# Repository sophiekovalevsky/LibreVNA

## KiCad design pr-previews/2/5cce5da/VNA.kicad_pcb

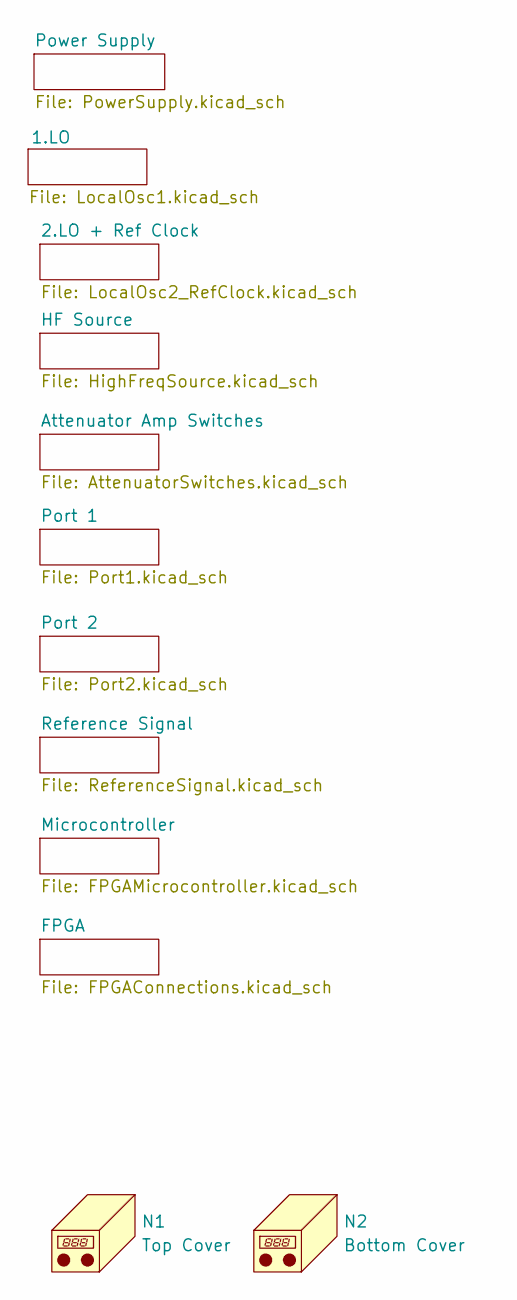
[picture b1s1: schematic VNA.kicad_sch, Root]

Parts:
N1: Top Cover; VNA_COVER_TOP
N2: Bottom Cover; VNA_COVER_BOTTOM

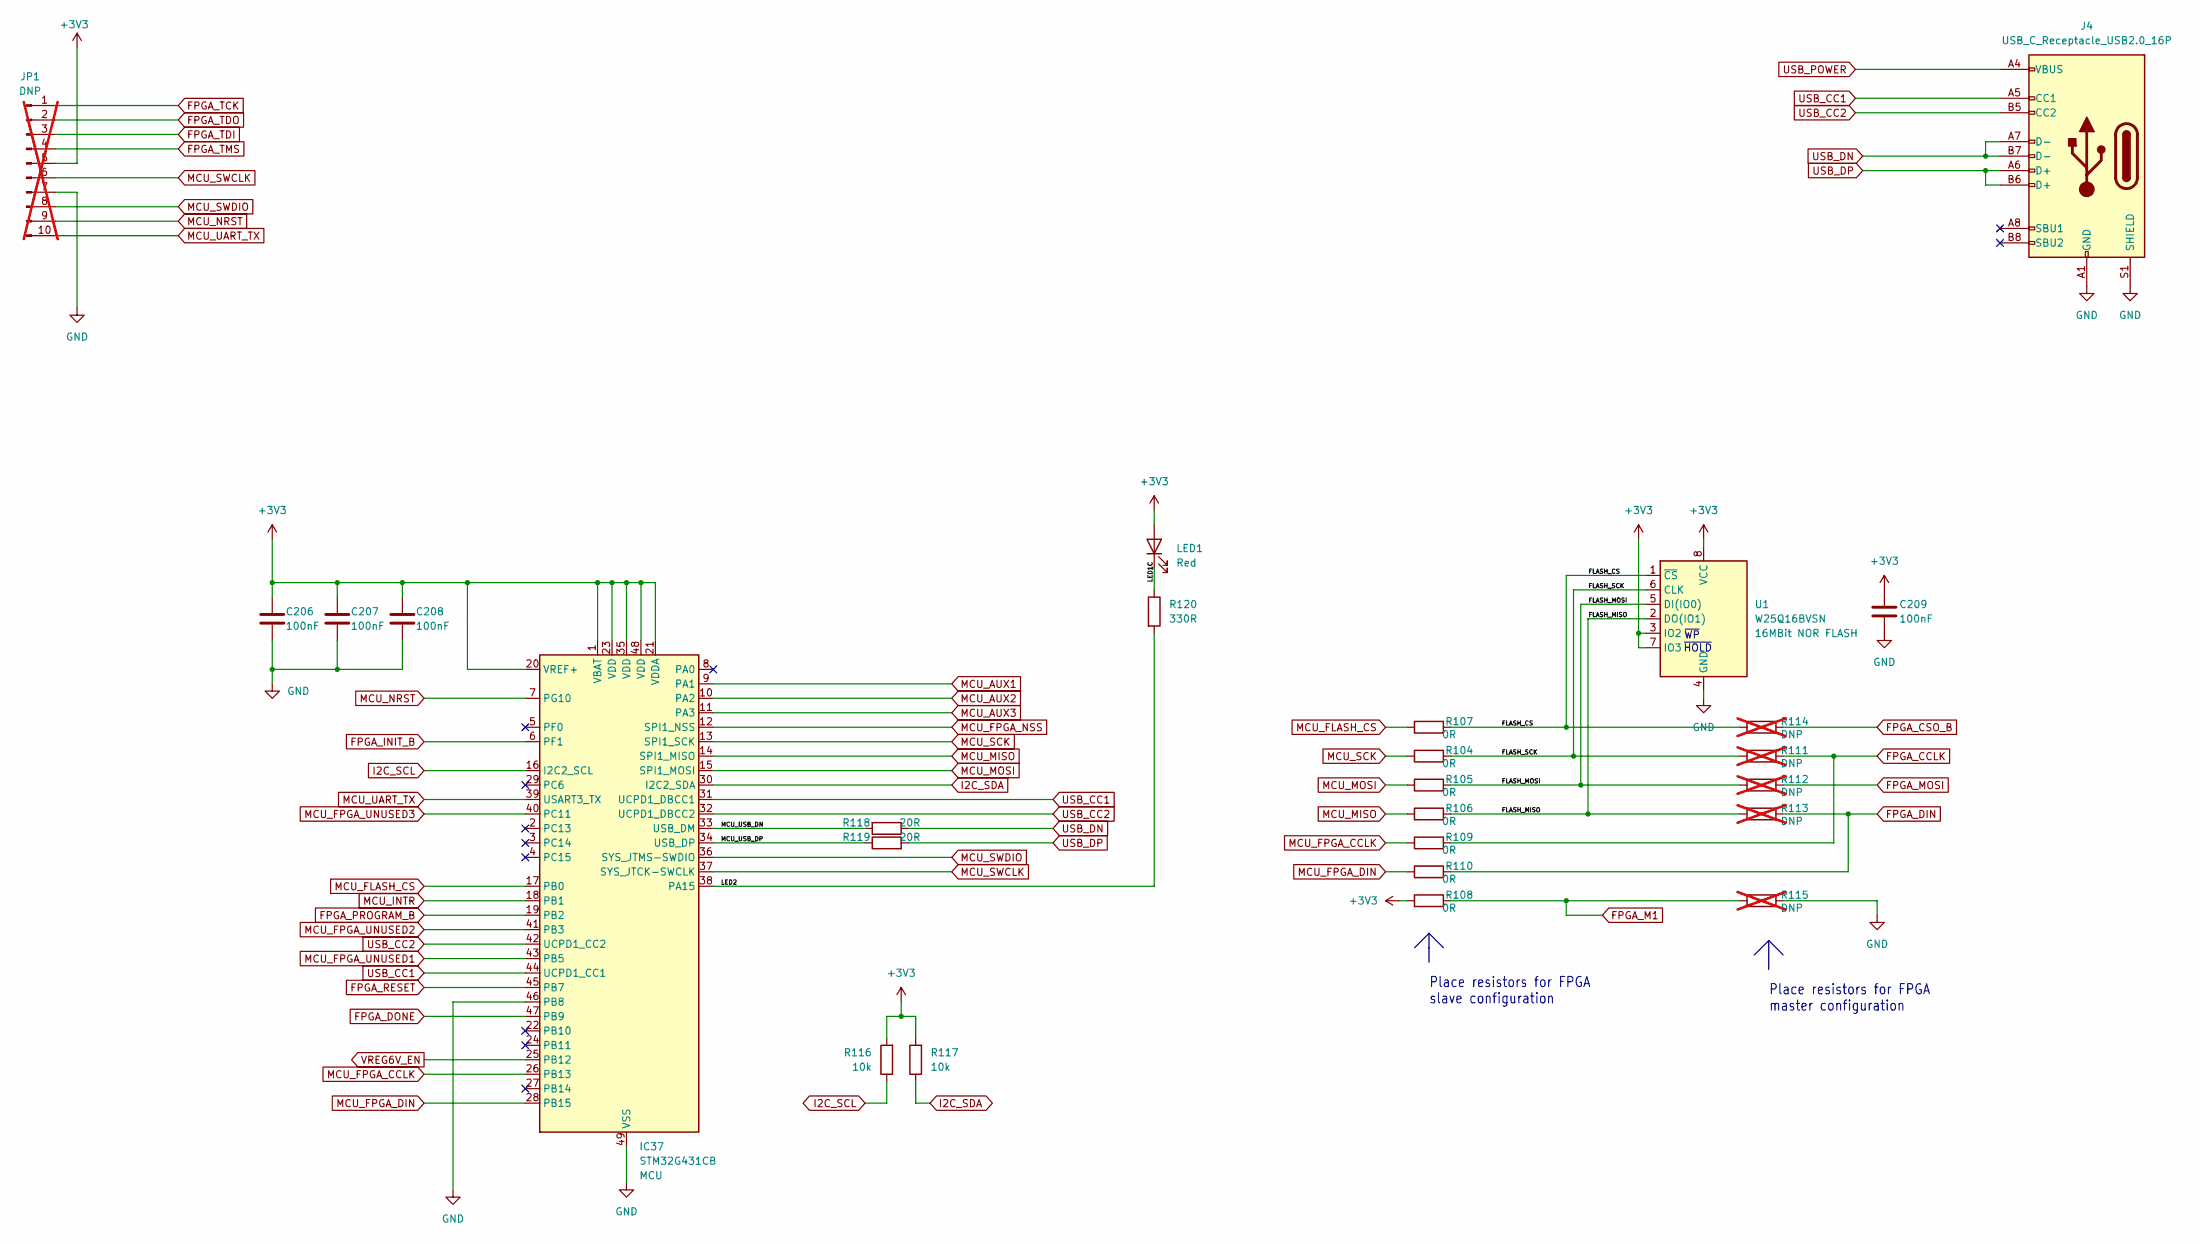
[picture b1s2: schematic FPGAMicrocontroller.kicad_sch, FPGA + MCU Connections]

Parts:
C206, C207, C208, C209: 100nF; C_0402_1005Metric
IC37: STM32G431CB; QFN-48-1EP_7x7mm_P0.5mm_EP5.6x5.6mm; MPN STM32G431CBU6
J4: USB_C_Receptacle_USB2.0_16P; USB_C_Receptacle_GCT_USB4105-xx-A_16P_TopMnt_Horizontal; MPN LCSC C668624
JP1: DNP; PinHeader_1x10_P2.54mm_Horizontal; not fitted
LED1: Red; LED_0603_1608Metric
R104, R105, R106, R107, R108, R109, R110: 0R; R_0402_1005Metric
R111, R112, R113, R114, R115: DNP; R_0402_1005Metric; not fitted
R116, R117: 10k; R_0402_1005Metric
R118, R119: 20R; R_0402_1005Metric
R120: 330R; R_0402_1005Metric
U1: W25Q16BVSN; SOIC-8_3.9x4.9mm_P1.27mm; MPN W25Q16JL

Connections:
+3V3: C206.1, C207.1, C208.1, C209.1, IC37.1 (VBAT), IC37.20 (VREF+), IC37.21 (VDDA), IC37.23 (VDD), IC37.35 (VDD), IC37.48 (VDD), JP1.5, LED1.2 (A), R108.1, R116.2, R117.2, U1.3 (IO2), U1.7 (IO3), U1.8 (VCC); also elsewhere on the board
/Microcontroller/FLASH_CS: R107.2, R114.1, U1.1 (~CS)
/Microcontroller/FLASH_MISO: R106.2, R113.1, U1.2 (DO(IO1))
/Microcontroller/FLASH_MOSI: R105.2, R112.1, U1.5 (DI(IO0))
/Microcontroller/FLASH_SCK: R104.2, R111.1, U1.6 (CLK)
/Microcontroller/LED1C: LED1.1 (K), R120.1
/Microcontroller/LED2: IC37.38 (PA15), R120.2
/Microcontroller/MCU_USB_DN: IC37.33 (USB_DM), R118.2
/Microcontroller/MCU_USB_DP: IC37.34 (USB_DP), R119.1
FPGA_CCLK: R109.2, R111.2; also elsewhere on the board
FPGA_CSO_B: R114.2; also elsewhere on the board
FPGA_DIN: R110.2, R113.2; also elsewhere on the board
FPGA_DONE: IC37.47 (PB9); also elsewhere on the board
FPGA_INIT_B: IC37.6 (PF1); also elsewhere on the board
FPGA_M1: R108.2, R115.1; also elsewhere on the board
FPGA_MOSI: R112.2; also elsewhere on the board
FPGA_PROGRAM_B: IC37.19 (PB2); also elsewhere on the board
FPGA_RESET: IC37.45 (PB7); also elsewhere on the board
FPGA_TCK: JP1.1; also elsewhere on the board
FPGA_TDI: JP1.3; also elsewhere on the board
FPGA_TDO: JP1.2; also elsewhere on the board
FPGA_TMS: JP1.4; also elsewhere on the board
GND: C206.2, C207.2, C208.2, C209.2, IC37.46 (PB8), IC37.49 (VSS), J4.A1 (GND), J4.A12 (GND), J4.B1 (GND), J4.B12 (GND), J4.S1 (SHIELD), JP1.7, R115.2, U1.4 (GND); also elsewhere on the board
I2C_SCL: IC37.16 (I2C2_SCL), R116.1; also elsewhere on the board
I2C_SDA: IC37.30 (I2C2_SDA), R117.1; also elsewhere on the board
MCU_AUX1: IC37.9 (PA1); also elsewhere on the board
MCU_AUX2: IC37.10 (PA2); also elsewhere on the board
MCU_AUX3: IC37.11 (PA3); also elsewhere on the board
MCU_FLASH_CS: IC37.17 (PB0), R107.1
MCU_FPGA_CCLK: IC37.26 (PB13), R109.1
MCU_FPGA_DIN: IC37.28 (PB15), R110.1
MCU_FPGA_NSS: IC37.12 (SPI1_NSS); also elsewhere on the board
MCU_FPGA_UNUSED1: IC37.43 (PB5); also elsewhere on the board
MCU_FPGA_UNUSED2: IC37.41 (PB3); also elsewhere on the board
MCU_FPGA_UNUSED3: IC37.40 (PC11); also elsewhere on the board
MCU_INTR: IC37.18 (PB1); also elsewhere on the board
MCU_MISO: IC37.14 (SPI1_MISO), R106.1; also elsewhere on the board
MCU_MOSI: IC37.15 (SPI1_MOSI), R105.1; also elsewhere on the board
MCU_NRST: IC37.7 (PG10), JP1.9
MCU_SCK: IC37.13 (SPI1_SCK), R104.1; also elsewhere on the board
MCU_SWCLK: IC37.37 (SYS_JTCK-SWCLK), JP1.6
MCU_SWDIO: IC37.36 (SYS_JTMS-SWDIO), JP1.8
MCU_UART_TX: IC37.39 (USART3_TX), JP1.10
USB_CC1: IC37.31 (UCPD1_DBCC1), IC37.44 (UCPD1_CC1), J4.A5 (CC1)
USB_CC2: IC37.32 (UCPD1_DBCC2), IC37.42 (UCPD1_CC2), J4.B5 (CC2)
USB_DN: J4.A7 (D-), J4.B7 (D-), R118.1
USB_DP: J4.A6 (D+), J4.B6 (D+), R119.2
USB_POWER: J4.A4 (VBUS), J4.A9 (VBUS), J4.B4 (VBUS), J4.B9 (VBUS); also elsewhere on the board
VREG6V_EN: IC37.25 (PB12); also elsewhere on the board

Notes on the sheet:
Place resistors for FPGA slave configuration
~{WP}
Place resistors for FPGA master configuration
~{HOLD}

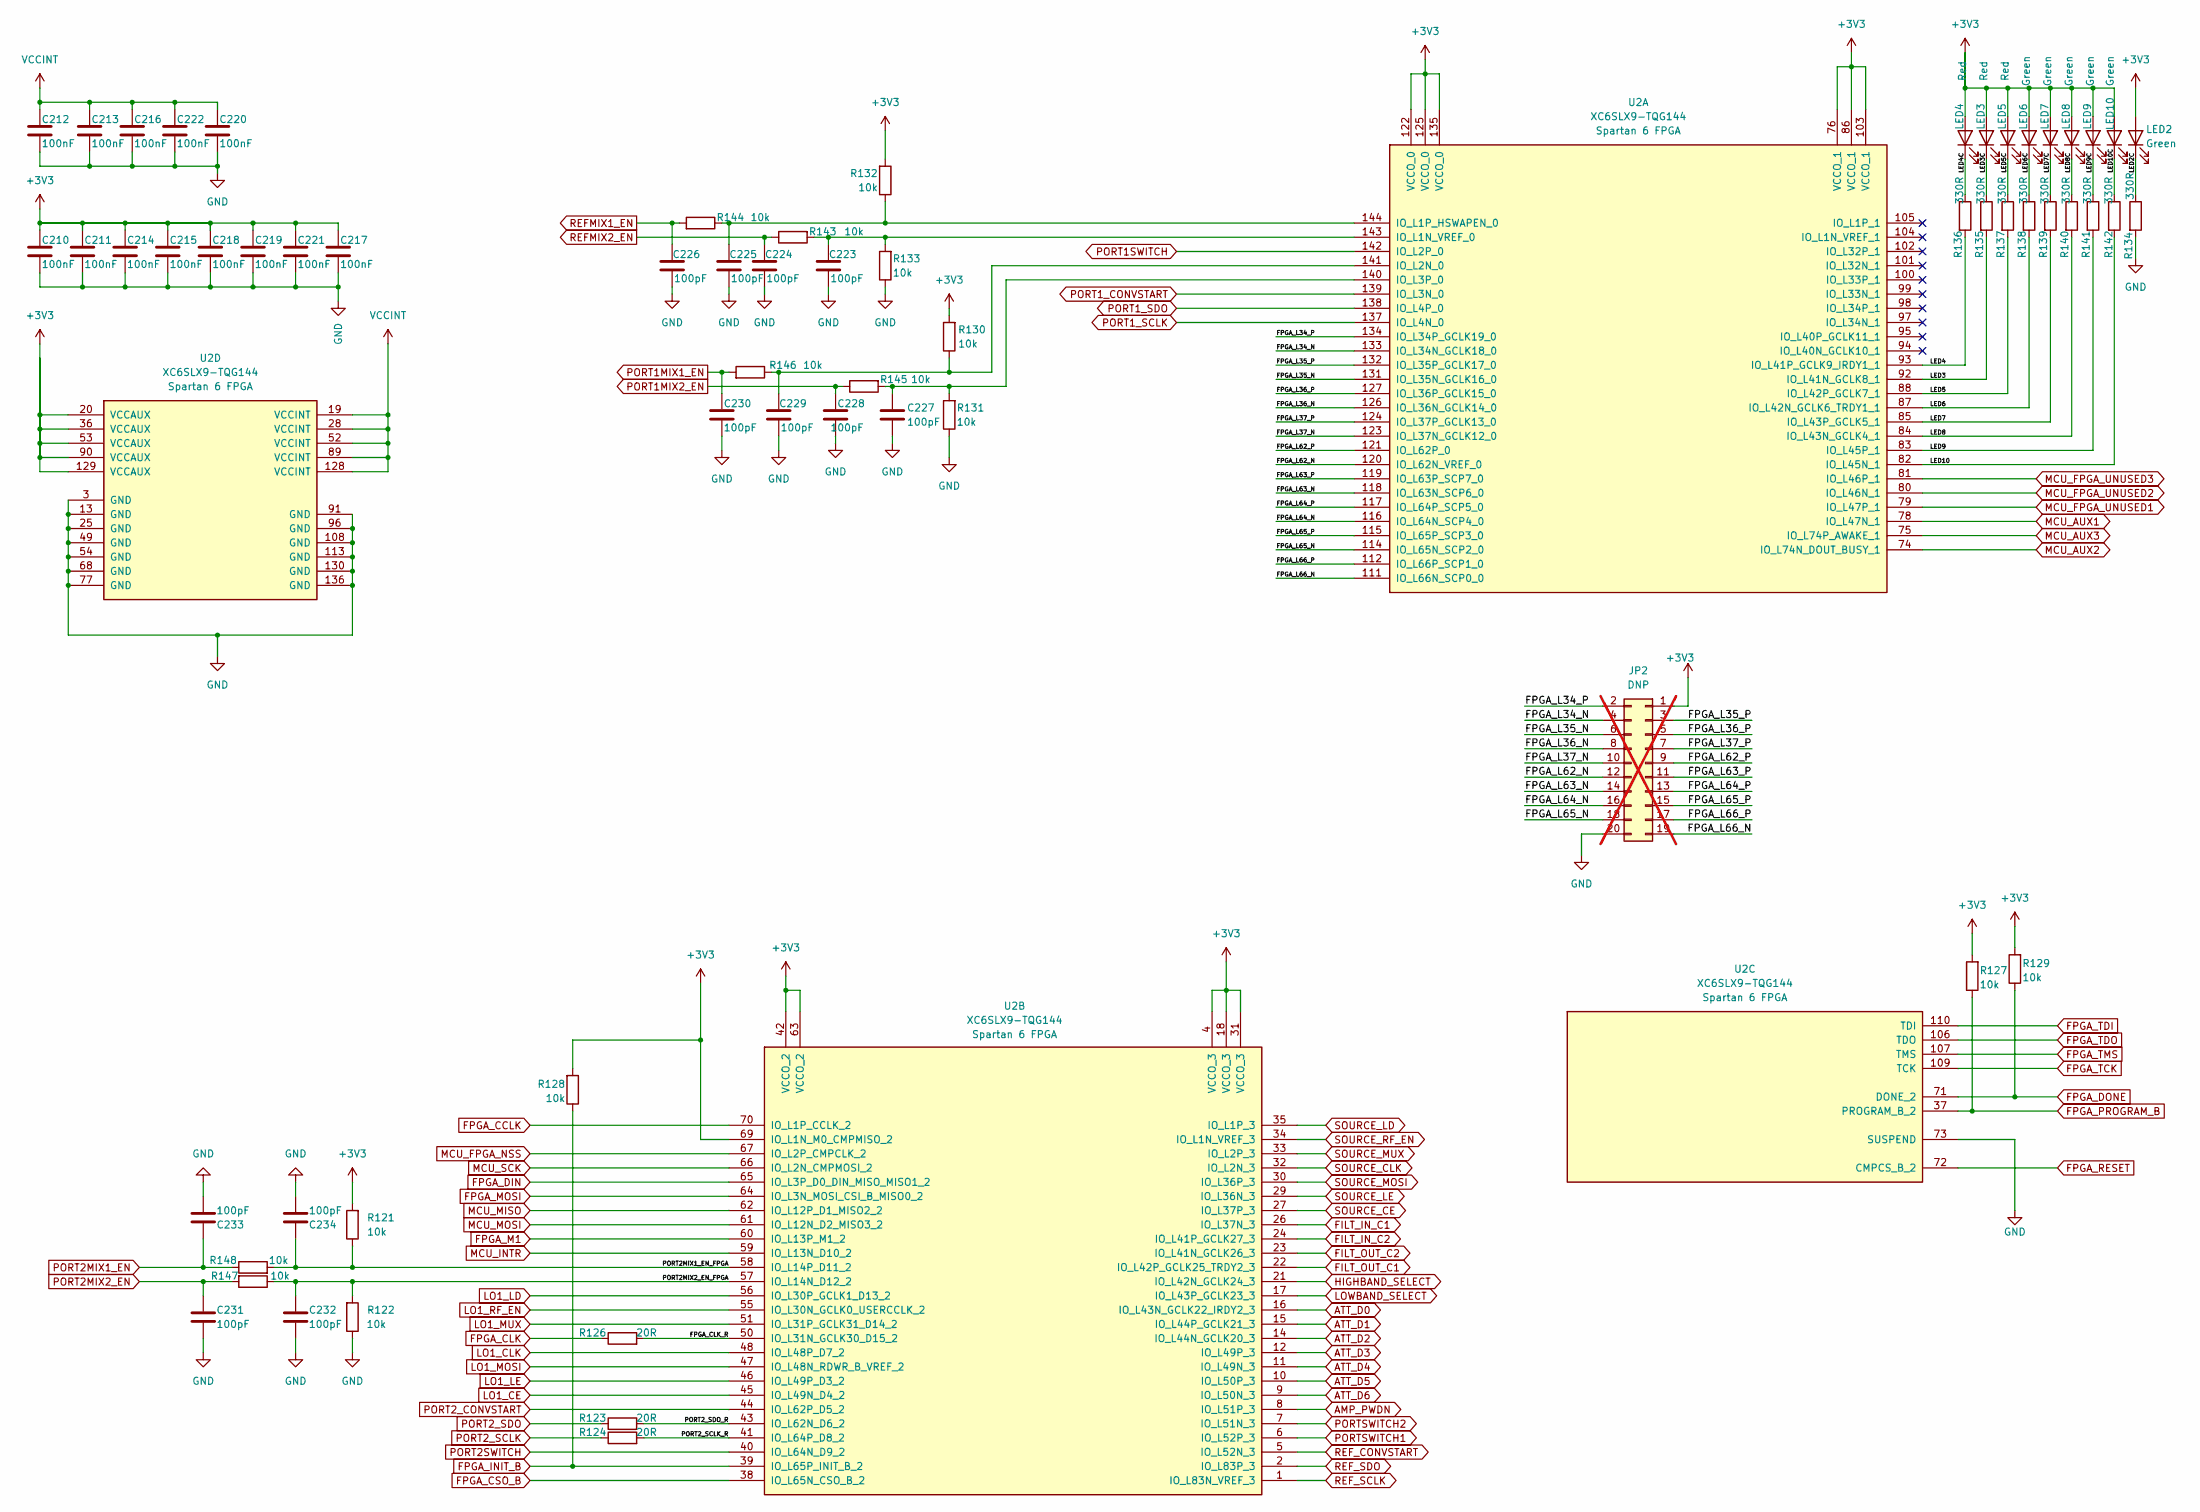
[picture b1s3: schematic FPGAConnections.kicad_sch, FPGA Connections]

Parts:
C210, C211, C212, C213, C214, C215, C216, C217, C218, C219, C220, C221, C222: 100nF; C_0402_1005Metric
C223, C224, C225, C226, C227, C228, C229, C230, C231, C232, C233, C234: 100pF; C_0402_1005Metric
JP2: DNP; PinHeader_2x10_P2.54mm_Vertical; not fitted
LED2, LED6, LED7, LED8, LED9, LED10: Green; LED_0603_1608Metric
LED3, LED4, LED5: Red; LED_0603_1608Metric
R121, R122, R127, R128, R129, R130, R131, R132, R133, R143, R144, R145, R146, R147, R148: 10k; R_0402_1005Metric
R123, R124, R126: 20R; R_0402_1005Metric
R134, R135, R136, R137, R138, R139, R140, R141, R142: 330R; R_0402_1005Metric
U2: XC6SLX9-TQG144; TQFP-144_20x20mm_P0.5mm; MPN XC6SLX9-2TQG144

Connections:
+3V3: C210.1, C211.1, C214.1, C215.1, C217.1, C218.1, C219.1, C221.1, JP2.1, LED2.2 (A), LED3.2 (A), LED4.2 (A), LED5.2 (A), LED6.2 (A), LED7.2 (A), LED8.2 (A), LED9.2 (A), LED10.2 (A), R121.2, R127.2, R128.2, R129.2, R130.2, R132.2, U2.4 (VCCO_3), U2.18 (VCCO_3), U2.20 (VCCAUX), U2.31 (VCCO_3), U2.36 (VCCAUX), U2.42 (VCCO_2), U2.53 (VCCAUX), U2.63 (VCCO_2), U2.69 (IO_L1N_M0_CMPMISO_2), U2.76 (VCCO_1), U2.86 (VCCO_1), U2.90 (VCCAUX), U2.103 (VCCO_1), U2.122 (VCCO_0), U2.125 (VCCO_0), U2.129 (VCCAUX), U2.135 (VCCO_0); also elsewhere on the board
/FPGA/FPGA_CLK_R: R126.2, U2.50 (IO_L31N_GCLK30_D15_2)
/FPGA/FPGA_L34_N: JP2.4, U2.133 (IO_L34N_GCLK18_0)
/FPGA/FPGA_L34_P: JP2.2, U2.134 (IO_L34P_GCLK19_0)
/FPGA/FPGA_L35_N: JP2.6, U2.131 (IO_L35N_GCLK16_0)
/FPGA/FPGA_L35_P: JP2.3, U2.132 (IO_L35P_GCLK17_0)
/FPGA/FPGA_L36_N: JP2.8, U2.126 (IO_L36N_GCLK14_0)
/FPGA/FPGA_L36_P: JP2.5, U2.127 (IO_L36P_GCLK15_0)
/FPGA/FPGA_L37_N: JP2.10, U2.123 (IO_L37N_GCLK12_0)
/FPGA/FPGA_L37_P: JP2.7, U2.124 (IO_L37P_GCLK13_0)
/FPGA/FPGA_L62_N: JP2.12, U2.120 (IO_L62N_VREF_0)
/FPGA/FPGA_L62_P: JP2.9, U2.121 (IO_L62P_0)
/FPGA/FPGA_L63_N: JP2.14, U2.118 (IO_L63N_SCP6_0)
/FPGA/FPGA_L63_P: JP2.11, U2.119 (IO_L63P_SCP7_0)
/FPGA/FPGA_L64_N: JP2.16, U2.116 (IO_L64N_SCP4_0)
/FPGA/FPGA_L64_P: JP2.13, U2.117 (IO_L64P_SCP5_0)
/FPGA/FPGA_L65_N: JP2.18, U2.114 (IO_L65N_SCP2_0)
/FPGA/FPGA_L65_P: JP2.15, U2.115 (IO_L65P_SCP3_0)
/FPGA/FPGA_L66_N: JP2.19, U2.111 (IO_L66N_SCP0_0)
/FPGA/FPGA_L66_P: JP2.17, U2.112 (IO_L66P_SCP1_0)
/FPGA/LED2C: LED2.1 (K), R134.1
/FPGA/LED3: R135.2, U2.92 (IO_L41N_GCLK8_1)
/FPGA/LED3C: LED3.1 (K), R135.1
/FPGA/LED4: R136.2, U2.93 (IO_L41P_GCLK9_IRDY1_1)
/FPGA/LED4C: LED4.1 (K), R136.1
/FPGA/LED5: R137.2, U2.88 (IO_L42P_GCLK7_1)
/FPGA/LED5C: LED5.1 (K), R137.1
/FPGA/LED6: R138.2, U2.87 (IO_L42N_GCLK6_TRDY1_1)
/FPGA/LED6C: LED6.1 (K), R138.1
/FPGA/LED7: R139.2, U2.85 (IO_L43P_GCLK5_1)
/FPGA/LED7C: LED7.1 (K), R139.1
/FPGA/LED8: R140.2, U2.84 (IO_L43N_GCLK4_1)
/FPGA/LED8C: LED8.1 (K), R140.1
/FPGA/LED9: R141.2, U2.83 (IO_L45P_1)
/FPGA/LED9C: LED9.1 (K), R141.1
/FPGA/LED10: R142.2, U2.82 (IO_L45N_1)
/FPGA/LED10C: LED10.1 (K), R142.1
/FPGA/PORT2MIX1_EN_FPGA: C234.1, R121.1, R148.2, U2.58 (IO_L14P_D11_2)
/FPGA/PORT2MIX2_EN_FPGA: C232.1, R122.2, R147.1, U2.57 (IO_L14N_D12_2)
/FPGA/PORT2_SCLK_R: R124.2, U2.41 (IO_L64P_D8_2)
/FPGA/PORT2_SDO_R: R123.2, U2.43 (IO_L62N_D6_2)
AMP_PWDN: U2.8 (IO_L51P_3); also elsewhere on the board
ATT_D0: U2.16 (IO_L43N_GCLK22_IRDY2_3); also elsewhere on the board
ATT_D1: U2.15 (IO_L44P_GCLK21_3); also elsewhere on the board
ATT_D2: U2.14 (IO_L44N_GCLK20_3); also elsewhere on the board
ATT_D3: U2.12 (IO_L49P_3); also elsewhere on the board
ATT_D4: U2.11 (IO_L49N_3); also elsewhere on the board
ATT_D5: U2.10 (IO_L50P_3); also elsewhere on the board
ATT_D6: U2.9 (IO_L50N_3); also elsewhere on the board
FILT_IN_C1: U2.26 (IO_L37N_3); also elsewhere on the board
FILT_IN_C2: U2.24 (IO_L41P_GCLK27_3); also elsewhere on the board
FILT_OUT_C1: U2.22 (IO_L42P_GCLK25_TRDY2_3); also elsewhere on the board
FILT_OUT_C2: U2.23 (IO_L41N_GCLK26_3); also elsewhere on the board
FPGA_CCLK: U2.70 (IO_L1P_CCLK_2); also elsewhere on the board
FPGA_CLK: R126.1; also elsewhere on the board
FPGA_CSO_B: U2.38 (IO_L65N_CSO_B_2); also elsewhere on the board
FPGA_DIN: U2.65 (IO_L3P_D0_DIN_MISO_MISO1_2); also elsewhere on the board
FPGA_DONE: R129.1, U2.71 (DONE_2); also elsewhere on the board
FPGA_INIT_B: R128.1, U2.39 (IO_L65P_INIT_B_2); also elsewhere on the board
FPGA_M1: U2.60 (IO_L13P_M1_2); also elsewhere on the board
FPGA_MOSI: U2.64 (IO_L3N_MOSI_CSI_B_MISO0_2); also elsewhere on the board
FPGA_PROGRAM_B: R127.1, U2.37 (PROGRAM_B_2); also elsewhere on the board
FPGA_RESET: U2.72 (CMPCS_B_2); also elsewhere on the board
FPGA_TCK: U2.109 (TCK); also elsewhere on the board
FPGA_TDI: U2.110 (TDI); also elsewhere on the board
FPGA_TDO: U2.106 (TDO); also elsewhere on the board
FPGA_TMS: U2.107 (TMS); also elsewhere on the board
GND: C210.2, C211.2, C212.2, C213.2, C214.2, C215.2, C216.2, C217.2, C218.2, C219.2, C220.2, C221.2, C222.2, C223.2, C224.2, C225.2, C226.2, C227.2, C228.2, C229.2, C230.2, C231.2, C232.2, C233.2, C234.2, JP2.20, R122.1, R131.1, R133.1, R134.2, U2.3 (GND), U2.13 (GND), U2.25 (GND), U2.49 (GND), U2.54 (GND), U2.68 (GND), U2.73 (SUSPEND), U2.77 (GND), U2.91 (GND), U2.96 (GND), U2.108 (GND), U2.113 (GND), U2.130 (GND), U2.136 (GND); also elsewhere on the board
HIGHBAND_SELECT: U2.21 (IO_L42N_GCLK24_3); also elsewhere on the board
LO1_CE: U2.45 (IO_L49N_D4_2); also elsewhere on the board
LO1_CLK: U2.48 (IO_L48P_D7_2); also elsewhere on the board
LO1_LD: U2.56 (IO_L30P_GCLK1_D13_2); also elsewhere on the board
LO1_LE: U2.46 (IO_L49P_D3_2); also elsewhere on the board
LO1_MOSI: U2.47 (IO_L48N_RDWR_B_VREF_2); also elsewhere on the board
LO1_MUX: U2.51 (IO_L31P_GCLK31_D14_2); also elsewhere on the board
LO1_RF_EN: U2.55 (IO_L30N_GCLK0_USERCCLK_2); also elsewhere on the board
LOWBAND_SELECT: U2.17 (IO_L43P_GCLK23_3); also elsewhere on the board
MCU_AUX1: U2.78 (IO_L47N_1); also elsewhere on the board
MCU_AUX2: U2.74 (IO_L74N_DOUT_BUSY_1); also elsewhere on the board
MCU_AUX3: U2.75 (IO_L74P_AWAKE_1); also elsewhere on the board
MCU_FPGA_NSS: U2.67 (IO_L2P_CMPCLK_2); also elsewhere on the board
MCU_FPGA_UNUSED1: U2.79 (IO_L47P_1); also elsewhere on the board
MCU_FPGA_UNUSED2: U2.80 (IO_L46N_1); also elsewhere on the board
MCU_FPGA_UNUSED3: U2.81 (IO_L46P_1); also elsewhere on the board
MCU_INTR: U2.59 (IO_L13N_D10_2); also elsewhere on the board
MCU_MISO: U2.62 (IO_L12P_D1_MISO2_2); also elsewhere on the board
MCU_MOSI: U2.61 (IO_L12N_D2_MISO3_2); also elsewhere on the board
MCU_SCK: U2.66 (IO_L2N_CMPMOSI_2); also elsewhere on the board
unnamed: C223.1, R133.2, R143.2, U2.143 (IO_L1N_VREF_0)
unnamed: C225.1, R132.1, R144.1, U2.144 (IO_L1P_HSWAPEN_0)
unnamed: C229.1, R130.1, R146.1, U2.141 (IO_L2N_0)
unnamed: C227.1, R131.2, R145.2, U2.140 (IO_L3P_0)
PORT1MIX1_EN: C230.1, R146.2; also elsewhere on the board
PORT1MIX2_EN: C228.1, R145.1; also elsewhere on the board
PORT1SWITCH: U2.142 (IO_L2P_0); also elsewhere on the board
PORT1_CONVSTART: U2.139 (IO_L3N_0); also elsewhere on the board
PORT1_SCLK: U2.137 (IO_L4N_0); also elsewhere on the board
PORT1_SDO: U2.138 (IO_L4P_0); also elsewhere on the board
PORT2MIX1_EN: C233.1, R148.1; also elsewhere on the board
PORT2MIX2_EN: C231.1, R147.2; also elsewhere on the board
PORT2SWITCH: U2.40 (IO_L64N_D9_2); also elsewhere on the board
PORT2_CONVSTART: U2.44 (IO_L62P_D5_2); also elsewhere on the board
PORT2_SCLK: R124.1; also elsewhere on the board
PORT2_SDO: R123.1; also elsewhere on the board
PORTSWITCH1: U2.6 (IO_L52P_3); also elsewhere on the board
PORTSWITCH2: U2.7 (IO_L51N_3); also elsewhere on the board
REFMIX1_EN: C226.1, R144.2; also elsewhere on the board
REFMIX2_EN: C224.1, R143.1; also elsewhere on the board
REF_CONVSTART: U2.5 (IO_L52N_3); also elsewhere on the board
REF_SCLK: U2.1 (IO_L83N_VREF_3); also elsewhere on the board
REF_SDO: U2.2 (IO_L83P_3); also elsewhere on the board
SOURCE_CE: U2.27 (IO_L37P_3); also elsewhere on the board
SOURCE_CLK: U2.32 (IO_L2N_3); also elsewhere on the board
SOURCE_LD: U2.35 (IO_L1P_3); also elsewhere on the board
SOURCE_LE: U2.29 (IO_L36N_3); also elsewhere on the board
SOURCE_MOSI: U2.30 (IO_L36P_3); also elsewhere on the board
SOURCE_MUX: U2.33 (IO_L2P_3); also elsewhere on the board
SOURCE_RF_EN: U2.34 (IO_L1N_VREF_3); also elsewhere on the board
VCCINT: C212.1, C213.1, C216.1, C220.1, C222.1, U2.19 (VCCINT), U2.28 (VCCINT), U2.52 (VCCINT), U2.89 (VCCINT), U2.128 (VCCINT); also elsewhere on the board

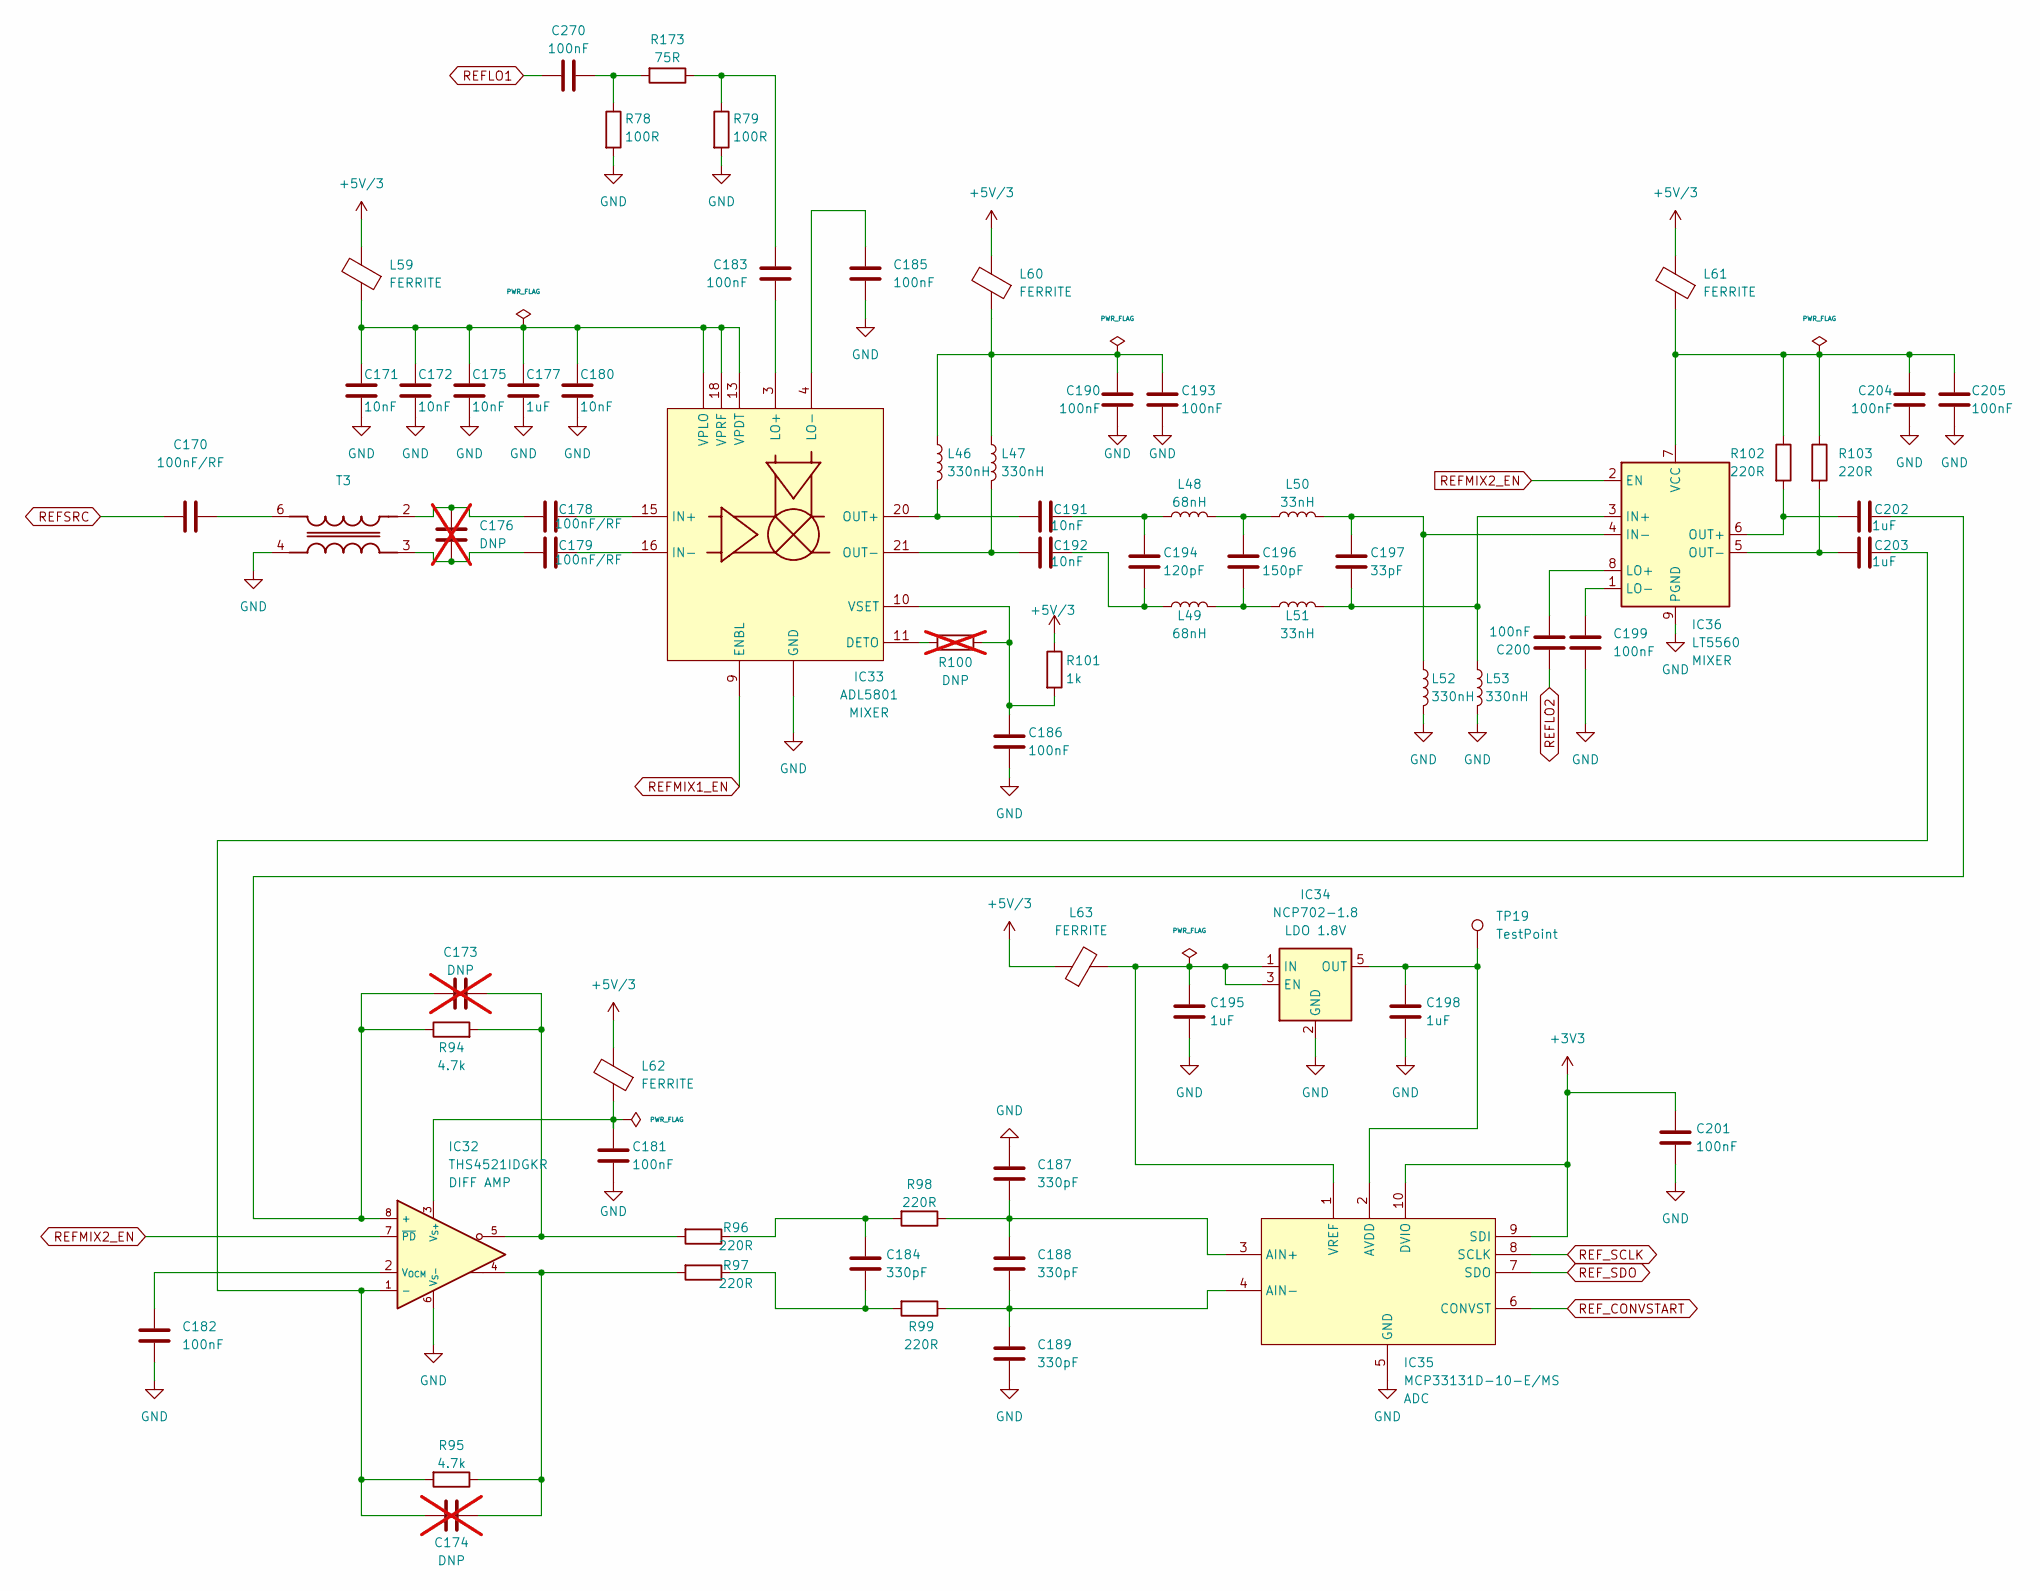
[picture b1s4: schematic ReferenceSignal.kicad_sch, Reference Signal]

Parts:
C170, C178, C179: 100nF/RF; C_0402_1005Metric
C171, C172, C175, C180, C191, C192: 10nF; C_0402_1005Metric
C173, C174, C176: DNP; C_0402_1005Metric; not fitted
C177, C195, C198, C202, C203: 1uF; C_0402_1005Metric
C181, C182, C183, C185, C186, C190, C193, C199, C200, C201, C204, C205, C270: 100nF; C_0402_1005Metric
C184, C187, C188, C189: 330pF; C_0402_1005Metric
C194: 120pF; C_0402_1005Metric
C196: 150pF; C_0402_1005Metric
C197: 33pF; C_0402_1005Metric
IC32: THS4521IDGKR; VSSOP-8_3.0x3.0mm_P0.65mm; MPN THS4521IDGKR
IC33: ADL5801; QFN-24-1EP_4x4mm_P0.5mm_EP2.6x2.6mm; MPN ADL5801
IC34: NCP702-1.8; SOT-23-5; MPN NCP702SN18T1G
IC35: MCP33131D-10-E/MS; VSSOP-10_3x3mm_P0.5mm; MPN MCP33131D-10-E/MS
IC36: LT5560; WSON-8-1EP_3x3mm_P0.5mm_EP1.45x2.4mm; MPN LT5560EDD
L46, L47, L52, L53: 330nH; L_0402_1005Metric; MPN LQW15CNR33J10D
L48, L49: 68nH; L_0402_1005Metric; MPN LQW15AN68NJ00D
L50, L51: 33nH; L_0402_1005Metric; MPN LQW15AN33NJ00D
L59, L60, L61, L62, L63: FERRITE; R_0402_1005Metric; MPN BLM15AX601SN1
R78, R79: 100R; R_0402_1005Metric
R94, R95: 4.7k; R_0402_1005Metric
R96, R97, R98, R99, R102, R103: 220R; R_0402_1005Metric
R100: DNP; R_0402_1005Metric; not fitted
R101: 1k; R_0402_1005Metric
R173: 75R; R_0402_1005Metric
T3: B012-617DB-1-63-B331; EASTEVER_BALUN; MPN B012-617DB-1-63-B331
TP19: TestPoint; B1,27

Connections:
+3V3: C201.2, IC35.9 (SDI), IC35.10 (DVIO); also elsewhere on the board
+5V/3: L59.2, L60.2, L61.2, L62.2, L63.1, R101.1; also elsewhere on the board
GND: C171.2, C172.2, C175.2, C177.2, C180.2, C181.1, C182.2, C185.2, C186.1, C187.1, C189.2, C190.2, C193.2, C195.2, C198.2, C199.1, C201.1, C204.1, C205.1, IC32.6 (V_{S-}), IC33.1 (GND), IC33.2 (GND), IC33.5 (GND), IC33.6 (GND), IC33.8 (GND), IC33.12 (GND), IC33.14 (GND), IC33.17 (GND), IC33.19 (GND), IC33.23 (GND), IC33.25 (GND), IC34.2 (GND), IC35.5 (GND), IC36.9 (PGND), L52.2, L53.2, R78.2, R79.2, T3.4 (OUT+); also elsewhere on the board
unnamed: C173.2, IC32.5, R94.2, R96.2
unnamed: C174.1, IC32.4, R95.1, R97.2
unnamed: C183.1, R79.1, R173.1
unnamed: C184.1, R96.1, R98.2
unnamed: C184.2, R97.1, R99.2
unnamed: C190.1, C193.1, L46.1, L47.1, L60.1
unnamed: C191.2, C194.1, L48.1
unnamed: C192.2, C194.2, L49.1
unnamed: C196.1, L48.2, L50.1
unnamed: C196.2, L49.2, L51.1
unnamed: C270.2, R78.1, R173.2
unnamed: C173.1, C202.2, IC32.8 (+), R94.1
unnamed: C174.2, C203.2, IC32.1 (-), R95.2
unnamed: C182.1, IC32.2 (V_{OCM})
unnamed: C181.2, IC32.3 (V_{S+}), L62.1
unnamed: IC33.11 (DETO), R100.2
unnamed: C178.2, IC33.15 (IN+)
unnamed: C179.2, IC33.16 (IN-)
unnamed: C183.2, IC33.3 (LO+)
unnamed: C185.1, IC33.4 (LO-)
unnamed: C191.1, IC33.20 (OUT+), L46.2
unnamed: C192.1, IC33.21 (OUT-), L47.2
unnamed: C171.1, C172.1, C175.1, C177.1, C180.1, IC33.7 (VPLO), IC33.13 (VPDT), IC33.18 (VPRF), IC33.24 (VPLO), L59.1
unnamed: C186.2, IC33.10 (VSET), R100.1, R101.2
unnamed: C195.1, IC34.1 (IN), IC34.3 (EN), IC35.1 (VREF), L63.2
unnamed: C198.1, IC34.5 (OUT), IC35.2 (AVDD), TP19.1
unnamed: C187.2, C188.1, IC35.3 (AIN+), R98.1
unnamed: C188.2, C189.1, IC35.4 (AIN-), R99.1
unnamed: C197.2, IC36.3 (IN+), L51.2, L53.1
unnamed: C197.1, IC36.4 (IN-), L50.2, L52.1
unnamed: C200.2, IC36.8 (LO+)
unnamed: C199.2, IC36.1 (LO-)
unnamed: C202.1, IC36.6 (OUT+), R102.2
unnamed: C203.1, IC36.5 (OUT-), R103.2
unnamed: C204.2, C205.2, IC36.7 (VCC), L61.1, R102.1, R103.1
unnamed: C176.1, C179.1, T3.3 (IN+)
unnamed: C176.2, C178.1, T3.2 (IN-)
unnamed: C170.2, T3.6 (OUT-)
REFLO1: C270.1; also elsewhere on the board
REFLO2: C200.1; also elsewhere on the board
REFMIX1_EN: IC33.9 (ENBL); also elsewhere on the board
REFMIX2_EN: IC32.7 (~PD), IC36.2 (EN); also elsewhere on the board
REFSRC: C170.1; also elsewhere on the board
REF_CONVSTART: IC35.6 (CONVST); also elsewhere on the board
REF_SCLK: IC35.8 (SCLK); also elsewhere on the board
REF_SDO: IC35.7 (SDO); also elsewhere on the board
